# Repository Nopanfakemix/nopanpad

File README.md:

# nopanpad
My wireless numpad project that doubles as a calculator

I have no goddamn idea how to use git :D

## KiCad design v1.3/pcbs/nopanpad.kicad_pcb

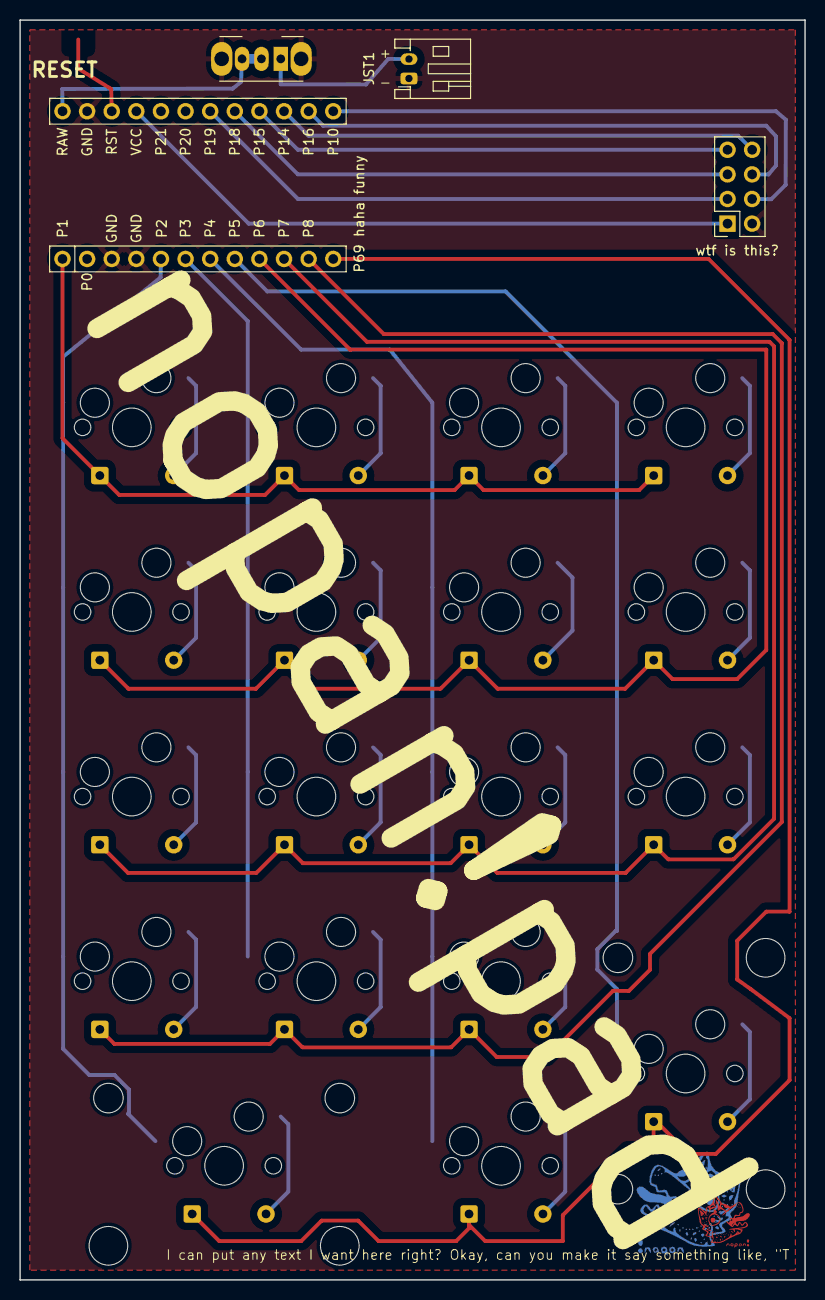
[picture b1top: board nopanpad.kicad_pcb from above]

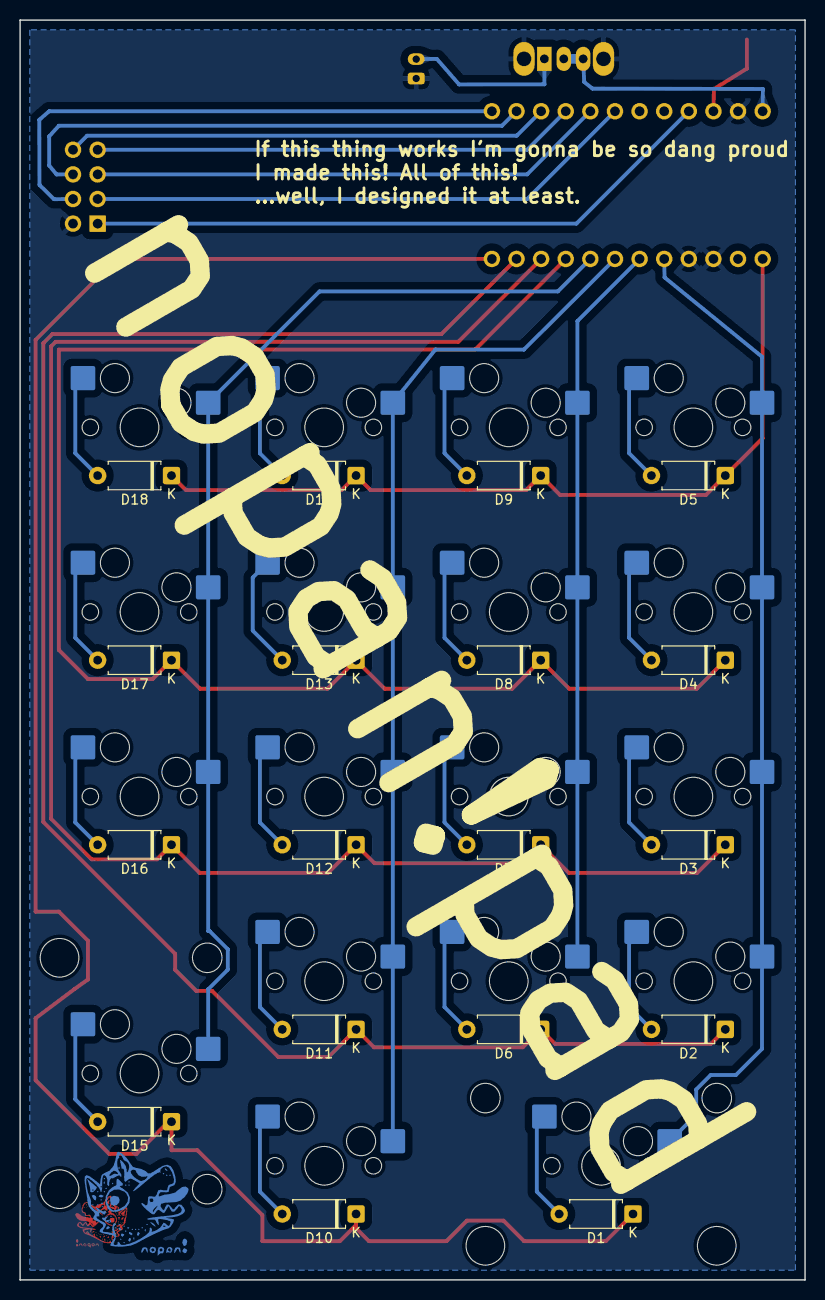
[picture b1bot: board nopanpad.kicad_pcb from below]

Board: 2 copper layers, 81.0 x 130.0 mm, 41 parts (37 on the bottom side), 35 nets.

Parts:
D1, D2, D3, D4, D5, D6, D7, D8, D9, D10, D11, D12, D13, D14, D15, D16, D17, D18: D_A-405_P7.62mm_Horizontal
JST1: JST_PH_S2B-PH-K_1x02_P2.00mm_Horizontal
MCU1: mcu_nice_nano
S1: MX-Hotswap-2U
S2, S3, S4, S5, S6, S7, S8, S9, S10, S11, S12, S13, S14, S16, S17, S18: MX-Hotswap-1U
S15: MX-Hotswap-2U-Vertical
nopan logo: nopan!; panicon_2.5mm
nopan!: nopan_logo; panicon_5mm
wtf is this?: PinSocket_2x04_P2.54mm_Vertical

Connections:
BUSY: MCU1.10, wtf is this?.8
CS: MCU1.8, wtf is this?.5
DC: MCU1.11, wtf is this?.6
GND: JST1.1, MCU1.2, MCU1.21, MCU1.22, wtf is this?.2
RES: MCU1.9, wtf is this?.7
SCL: MCU1.12, wtf is this?.4
SDA: MCU1.7, wtf is this?.3
VCC: MCU1.4, wtf is this?.1
col1: MCU1.20, S1.1, S2.1, S3.1, S4.1, S5.1
col1_row1: D1.2, S1.2
col1_row2: D2.2, S2.2
col1_row3: D3.2, S3.2
col1_row4: D4.2, S4.2
col1_row5: D5.2, S5.2
col2: MCU1.19, S6.1, S7.1, S8.1, S9.1
col2_row2: D6.2, S6.2
col2_row3: D7.2, S7.2
col2_row4: D8.2, S8.2
col2_row5: D9.2, S9.2
col3: MCU1.18, S10.1, S11.1, S12.1, S13.1, S14.1
col3_row1: D10.2, S10.2
col3_row2: D11.2, S11.2
col3_row3: D12.2, S12.2
col3_row4: D13.2, S13.2
col3_row5: D14.2, S14.2
col4: MCU1.17, S15.1, S16.1, S17.1, S18.1
col4_row1: D15.2, S15.2
col4_row3: D16.2, S16.2
col4_row4: D17.2, S17.2
col4_row5: D18.2, S18.2
row1: D1.1, D10.1, D15.1, MCU1.13
row2: D2.1, D6.1, D11.1, MCU1.14
row3: D3.1, D7.1, D12.1, D16.1, MCU1.15
row4: D4.1, D8.1, D13.1, D17.1, MCU1.16
row5: D5.1, D9.1, D14.1, D18.1, MCU1.24

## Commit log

2026-01-11 Update README.md
    Uhhhhhhhhhhhhhh
2026-01-11 Add v1.3
    Already created a few iterations by this point
2026-01-11 Create put code here.txt
    Get bent X2
2026-01-12 Create Calc V1.ino
    Super fucked, created with temporary stuff for testing in Wokwiki simulator. Sim seems to be super buggy in certain situations. how does one use github. what is a git besides a british insult?
2026-01-13 Update Calc V1.ino
    Code less scuffed. figured out why the wokwiki sim was busted. it mostly works as a calculator im just making it better now
2026-01-16 Update Calc V1.ino
    Changed again! working in Wokwi widda 20x4 LCD for diag, gotta go to sleep and need to save my code nobody is ever gonna read this not even me! If anyone in the future wanted this note to be helpful 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
2026-01-17 Update Calc V1.ino
    did anything change this time
2026-01-18 Update Calc V1.ino
    OKAY code actually works now! further testing required within Wokwi sim
